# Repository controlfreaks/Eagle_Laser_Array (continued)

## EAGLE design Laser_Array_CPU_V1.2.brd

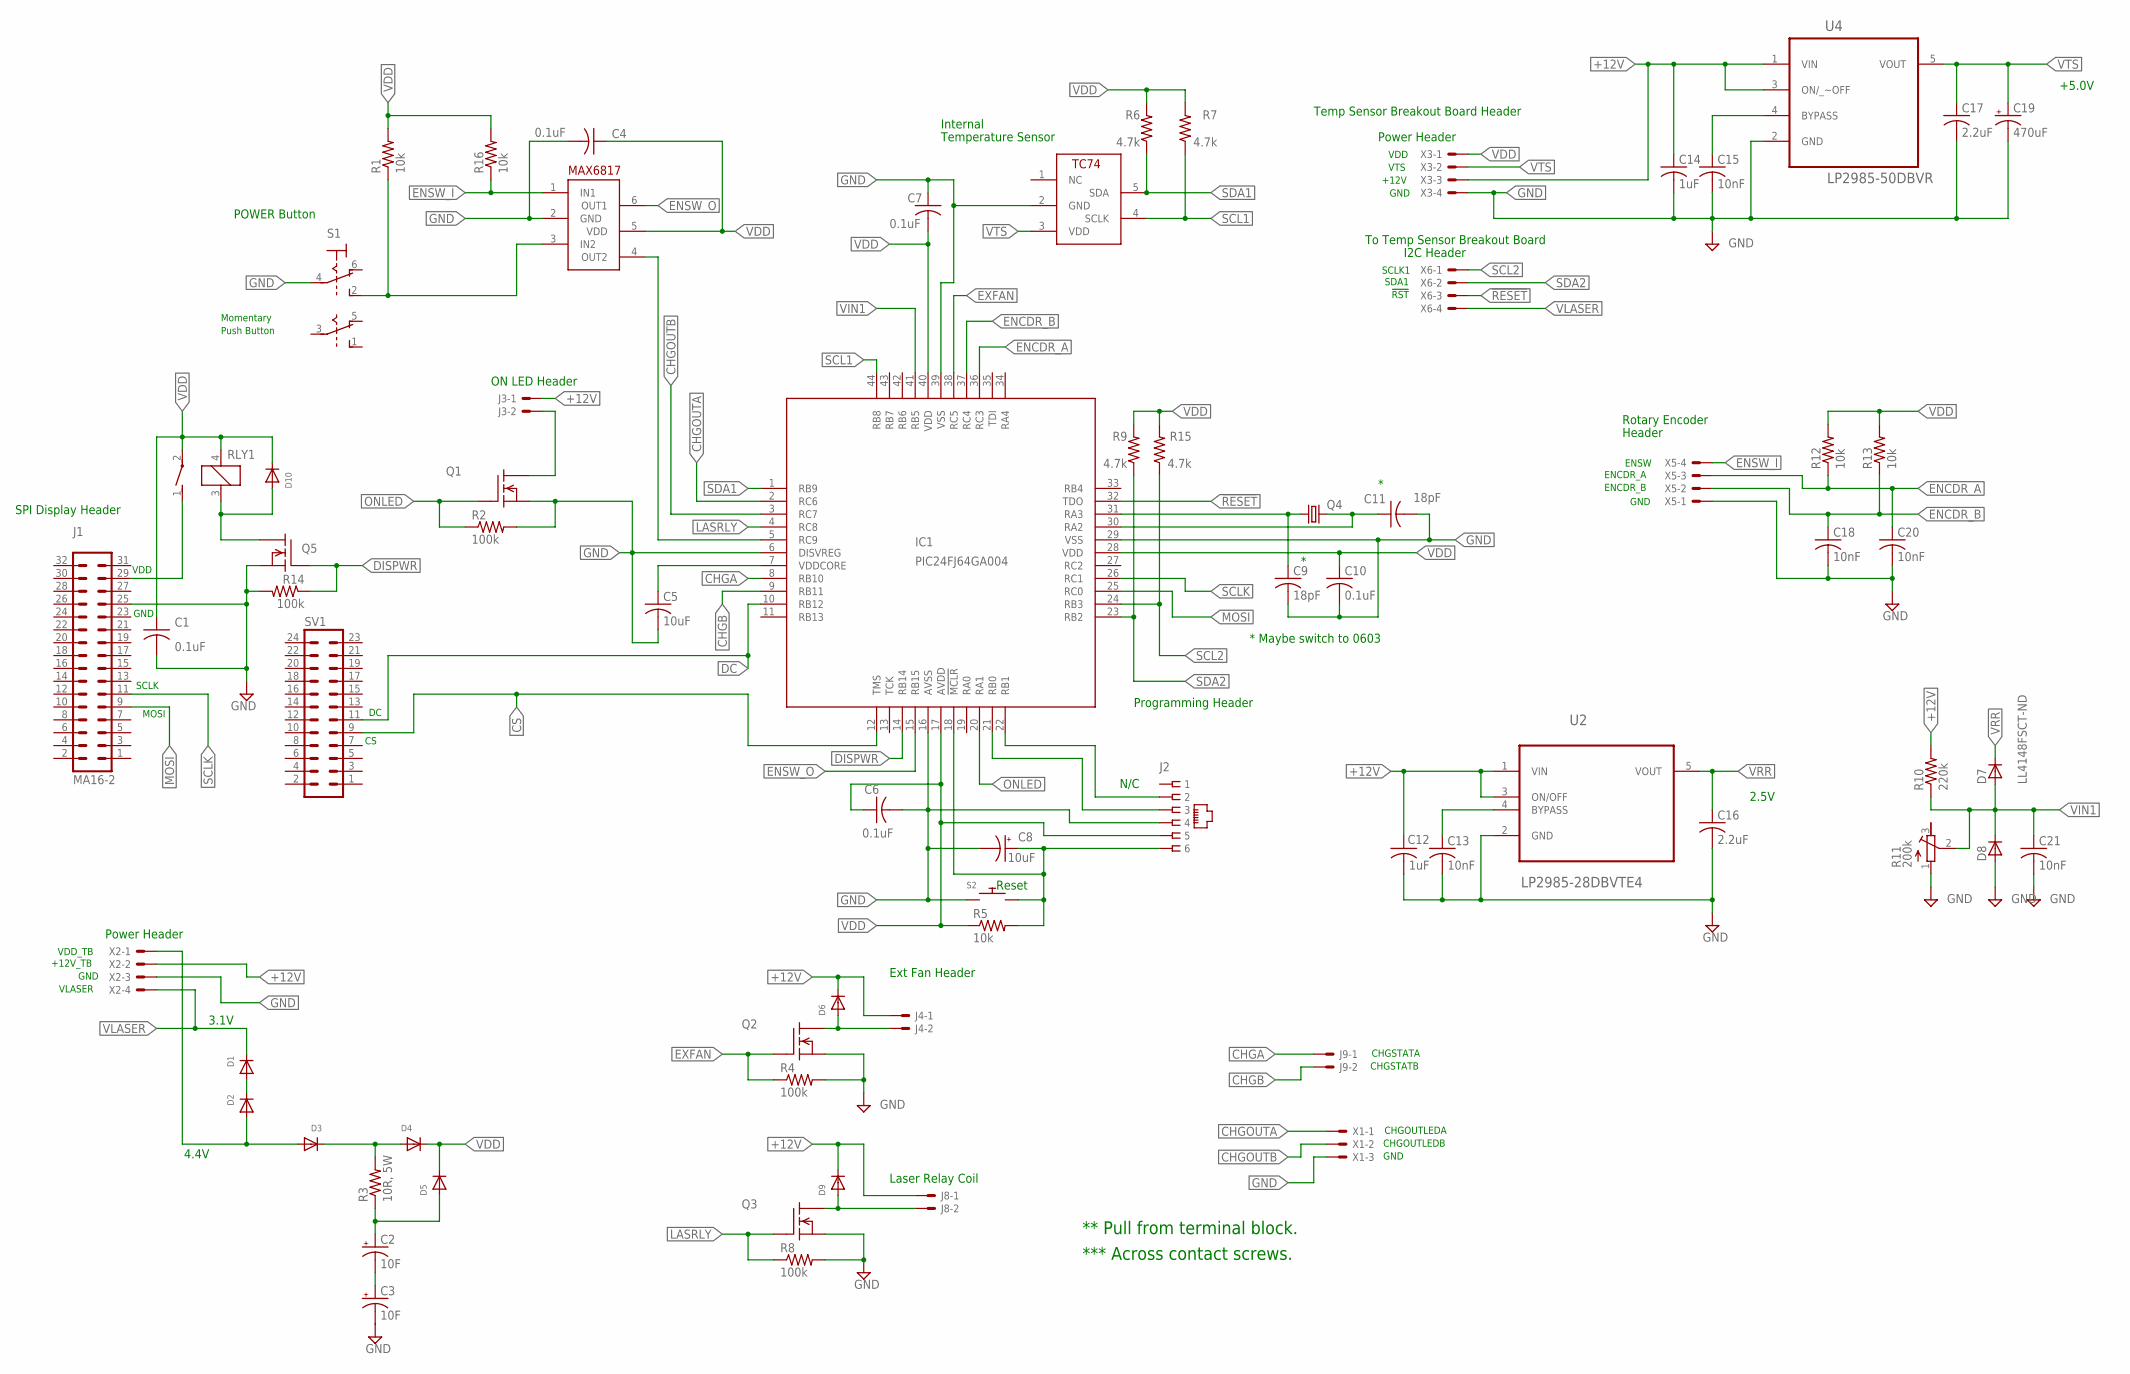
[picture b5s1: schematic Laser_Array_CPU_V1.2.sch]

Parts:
C1, C4, C6, C7, C10: 0.1uF; C0805
C2, C3: 10F; E5-10,5
C5: 10uF; C0805
C8: 10uF; CAP3X3
C9, C11: 18pF; C0805
C12, C14: 1uF; C0805
C13, C15, C18, C20, C21: 10nF; C0805
C16, C17: 2.2uF; C0805
C19: 470uF; PANASONIC_F
D1, D2, D3: S10M-TPMSCT_ND; S10M-TPMSCT-ND
D4, D5, D6, D9, D10: DIODE_GENPURP_1A_100V; DO214AC
D7, D8: LL4148FSCT-ND; SOD80
IC1: PIC24FJ64GA004; TQFP44
J1: MA16-2
J2: RJ_25; RJ11-NO_SHIELD
J3, J4, J8, J9: 22-23-2021
Q1, Q2, Q3, Q5: QS5U34CT-ND_MOSFET_N_CHANNEL; SOT23-5L
Q4: CRYSTALSM49; SM49
R1, R5, R16: 10k; R0805
R2, R4, R8, R14: 100k; R0805
R3: 10R, 5W; RESISTOR5W
R6, R7, R9, R15: 4.7k; M0805
R10: 220k; M0805
R11: 200k; RTRIM3224X
R12, R13: 10k; M0805
RLY1: RELAY_SPST_1A
S1: DPDT_TOGGLE; 22-23-2061
S2: TACT_PB; PUSHBUTTON_SMD_SJ
S3: TC74; SOT23-5L
SV1: MA12-2
U1: MAX6817; SOT23-6
U2: LP2985-28DBVTE4; SOT95P280X145-5N
U4: LP2985-50DBVR; SOT95P280X145-5N
X1: 22-23-2031
X2, X3, X5, X6: 22-23-2041

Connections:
!RESET: IC1.32 (TDO), X6.3
+12V: C12.1, C14.1, D6.C, D9.C, J3.1, J4.1, J8.1, R10.2, U2.1 (VIN), U2.3 (ON/OFF), U4.1 (VIN), U4.3 (ON/_~OFF), X2.2, X3.3
CHGA: IC1.8 (RB10), J9.1
CHGB: IC1.9 (RB11), J9.2
CHGOUTA: IC1.2 (RC6), X1.1
CHGOUTB: IC1.3 (RC7), X1.2
CS: IC1.12 (TMS), SV1.9
DC: IC1.10 (RB12), SV1.11
DISPWR: IC1.14 (RB14), Q5.1 (G), R14.1
ENCDR_A: C20.1, IC1.36 (RC3), R12.1, X5.3
ENCDR_B: C18.1, IC1.37 (RC4), R13.1, X5.2
ENSW_I: R16.1, U1.1 (IN1), X5.4
ENSW_O: IC1.15 (RB15), U1.6 (OUT1)
EXFAN: IC1.38 (RC5), Q2.1 (G), R4.1
GND: C1.2, C3.-, C4.2, C5.2, C6.2, C7.1, C8.-, C9.2, C10.2, C11.2, C12.2, C13.2, C14.2, C15.2, C16.2, C17.2, C18.2, C19.-, C20.2, C21.2, D8.2 (A), IC1.6 (DISVREG), IC1.16 (AVSS), IC1.29 (VSS), IC1.39 (VSS), J1.25, J2.4, Q1.2 (S), Q2.2 (S), Q3.2 (S), Q5.2 (S), R2.2, R4.2, R8.2, R11.1 (A), R14.2, S1.4, S2.1, S2.2 (1), S3.2 (GND), U1.2 (GND), U2.2 (GND), U4.2 (GND), X1.3, X2.3, X3.4, X5.1
LASRLY: IC1.4 (RC8), Q3.1 (G), R8.1
MOSI: IC1.25 (RC0), J1.9
unnamed: C8.+, IC1.18 (!MCLR), J2.6, R5.2, S2.3 (2), S2.4 (2)
unnamed: C5.1, IC1.7 (VDDCORE)
unnamed: D1.A, D2.C
unnamed: IC1.22 (RB1), J2.2
unnamed: C9.1, IC1.31 (RA3), Q4.1
unnamed: C11.1, IC1.30 (RA2), Q4.2
unnamed: D10.A, Q5.5 (D), RLY1.3 (1)
unnamed: R1.1, S1.2 (S), U1.3 (IN2)
unnamed: IC1.5 (RC9), U1.4 (OUT2)
unnamed: J3.2, Q1.5 (D)
unnamed: D6.A, J4.2, Q2.5 (D)
unnamed: D9.A, J8.2, Q3.5 (D)
unnamed: J1.29, RLY1.1 (S)
unnamed: C15.1, U4.4 (BYPASS)
unnamed: IC1.21 (RB0), J2.3
unnamed: D3.C, D4.A, R3.2
unnamed: C2.-, C3.+
unnamed: C2.+, D5.A, R3.1
unnamed: C13.1, U2.4 (BYPASS)
ONLED: IC1.20 (RA1), Q1.1 (G), R2.1
SCL1: IC1.44 (RB8), R7.1, S3.4 (SCLK)
SCL2: IC1.24 (RB3), R15.1, X6.1
SCLK: IC1.26 (RC1), J1.11
SDA1: IC1.1 (RB9), R6.1, S3.5 (SDA)
SDA2: IC1.23 (RB2), R9.1, X6.2
VDD: C1.1, C4.1, C6.1, C7.2, C10.1, D4.C, D5.C, D10.C, IC1.17 (AVDD), IC1.28 (VDD), IC1.40 (VDD), J2.5, R1.2, R5.1, R6.2, R7.2, R9.2, R12.2, R13.2, R15.2, R16.2, RLY1.2, RLY1.4 (2), U1.5 (VDD), X3.1
VDD_TB: D2.A, D3.A, X2.1
VIN1: C21.1, D7.2 (A), D8.1 (C), IC1.41 (RB5), R10.1, R11.2 (S)
VLASER: D1.C, X2.4, X6.4
VRR: C16.1, D7.1 (C), U2.5 (VOUT)
VTS: C17.1, C19.+, S3.3 (VDD), U4.5 (VOUT), X3.2

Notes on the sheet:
Programming Header
N/C
* Maybe switch to 0603
Reset
SPI Display Header
VDD
GND
SCLK
MOSI
Momentary
Push Button
POWER Button
Internal
Temperature Sensor
2.5V
Rotary Encoder
ENSW
ENCDR_A
ENCDR_B
Header
CHGSTATA
CHGSTATB
I2C Header
SCLK1
SDA1
!RST
Power Header
+12V
Temp Sensor Breakout Board Header
To Temp Sensor Breakout Board
CHGOUTLEDA
CHGOUTLEDB
ON LED Header
VTS
Laser Relay Coil
** Pull from terminal block.
4.4V
3.1V
VDD_TB
+12V_TB

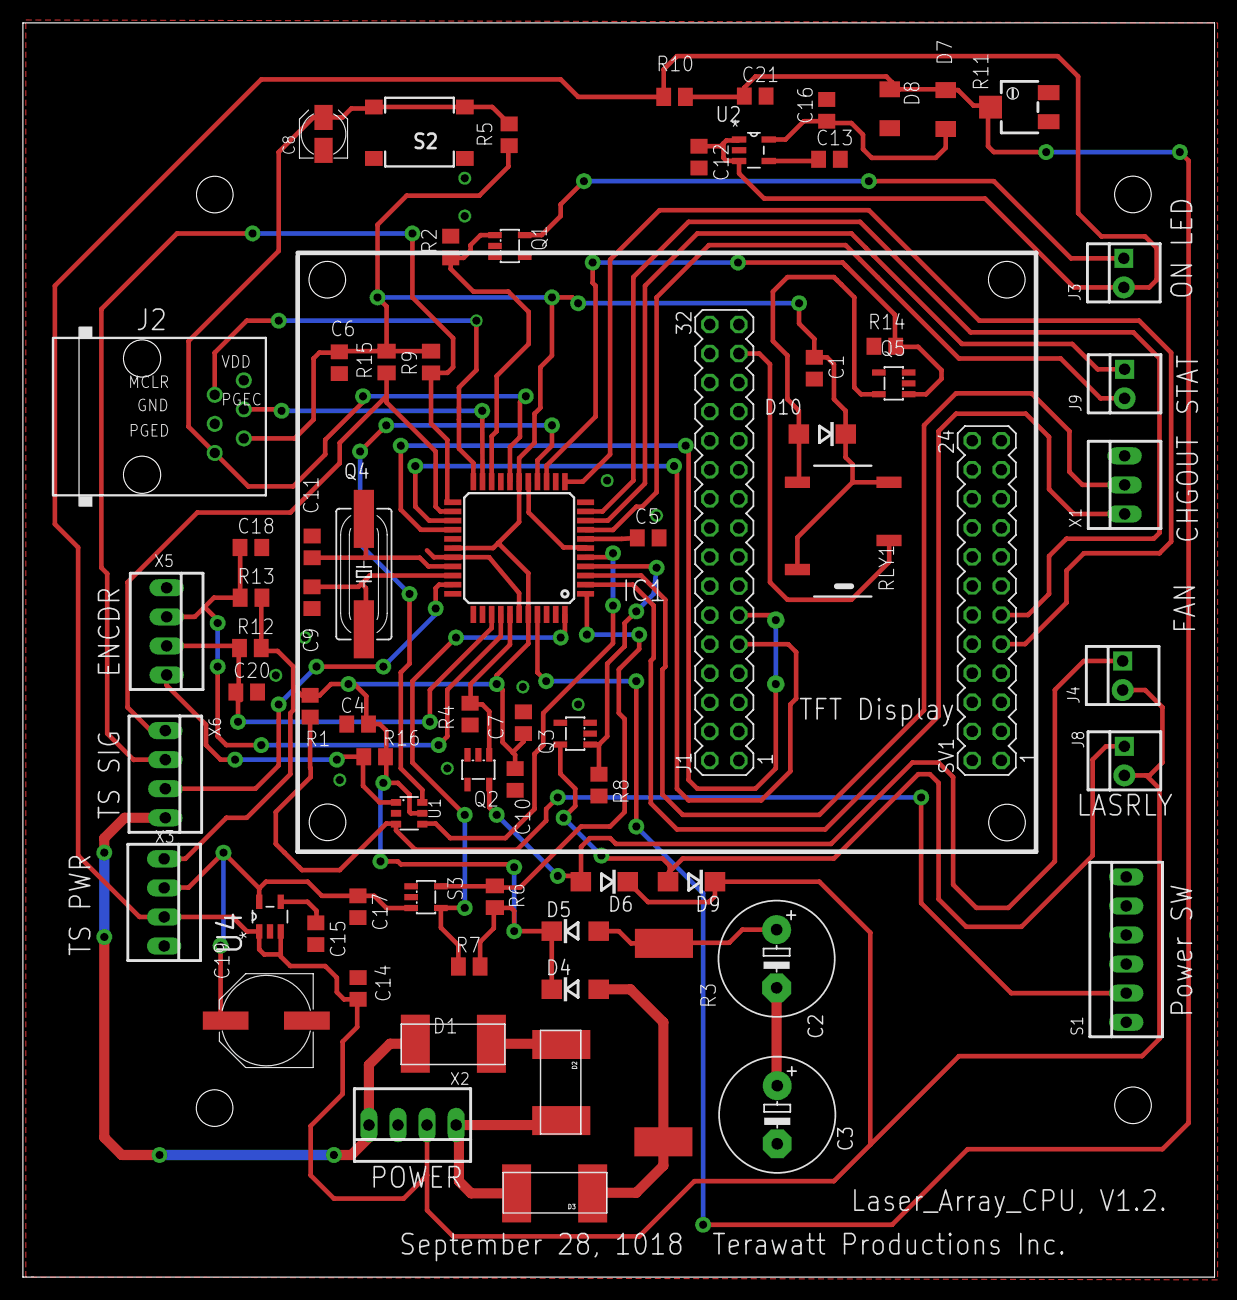
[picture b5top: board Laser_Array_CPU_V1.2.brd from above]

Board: 2 copper layers, 104.1 x 109.6 mm, 72 parts (0 on the bottom side), 48 nets.

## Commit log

2018-06-29 second commit
2018-07-09 July 9
2018-07-09 commit before push
2018-07-09 added temp sensors
2018-07-10 added temp sensors as breakout board
2018-07-10 commit on surface
2018-07-10 commit on surface 2
2018-07-10 altered for surface
2018-07-11 added MCU decoupling capacitor C17
2018-07-11 added CS and DC to schematic
2018-07-23 Started CPU Board
2018-09-13 temperture sensor board & CPU board complete
2018-09-13 temperture sensor board & CPU board complete, this time saved.
2018-09-18 CPU board with headers moved over and with programming jack. V1.0
2018-09-18 Temperature_Sensor board, changed traces from 14 to 16, V1.1
2018-09-18 Temperature_Sensor board, changed traces from 14 to 16, V1.1, again
2018-09-18 CPU board changed, made a little narrower. V1.2
2018-09-18 CPU board changed, made a little narrower. V1.2, again, again
2018-09-18 Temperature_Sensor board, changed traces from 14 to 16, V1.1, again, again
2018-09-18 Charging Board header change, V1.1
2018-09-19 Charging Board header change, V1.1, again
2018-10-02 Finished Laser_Array_V1.2
2018-10-16 Finished Laser_Array_Temp_Low_BRD_V2.0 and Laser_Array_Temp_High_BRD_V1.0 boards
2018-10-29 Changed Temperature_sensor_Board2 Oct 28/2018
2018-11-19 Finished Laser_Array next versions, all theee boards, Nov19_2018
2018-11-28 Finished Laser_Array next versions, all three boards including revised charger board
2019-03-06 Finished Laser_Array CPU Board V 1.5
2019-03-20 Updating the Laser Array Chassis wiring diagram
